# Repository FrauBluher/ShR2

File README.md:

ShR2
====

A redesign of the SHEMP system with a focus on high-bandwidth data acquisition.

Design information and supporting documentation can be found in this repository.

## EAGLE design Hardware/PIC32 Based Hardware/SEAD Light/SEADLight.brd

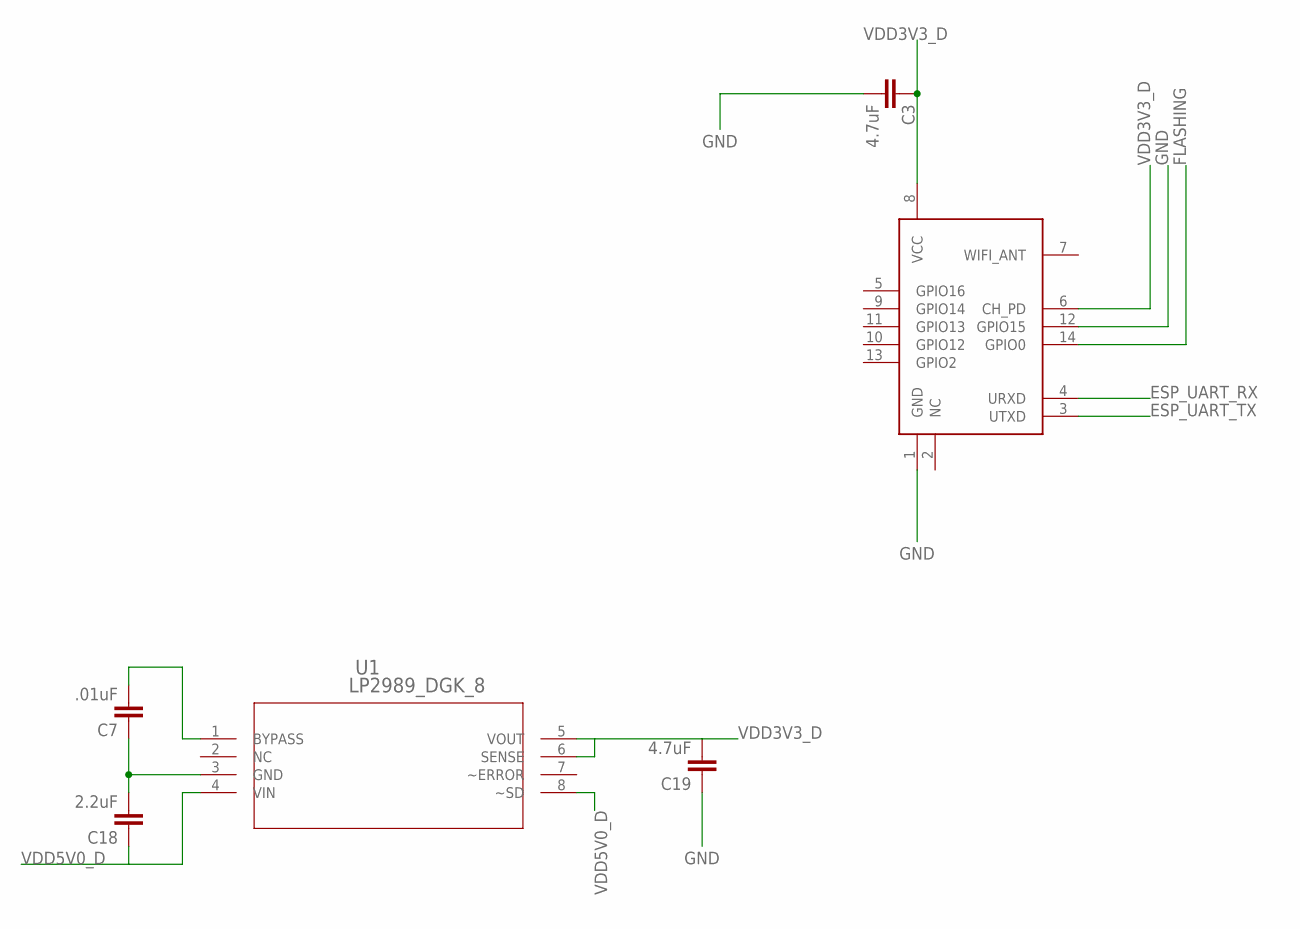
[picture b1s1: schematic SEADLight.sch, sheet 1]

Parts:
C3, C19: 4.7uF; 0805
C7: .01uF; 0805
C18: 2.2uF; 0805
U1: LP2989_DGK_8; MUA08A
U$3: EPS8266; ESP8266-03

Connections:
ESP_UART_RX: U$3.4 (URXD); also elsewhere on the board
ESP_UART_TX: U$3.3 (UTXD); also elsewhere on the board
FLASHING: U$3.14 (GPIO0)
GND: C3.2, C7.1, C18.2, C19.1, U1.3 (GND), U$3.1 (GND), U$3.12 (GPIO15); also elsewhere on the board
unnamed: C7.2, U1.1 (BYPASS)
VDD3V3_D: C3.1, C19.2, U1.5 (VOUT), U1.6 (SENSE), U$3.6 (CH_PD), U$3.8 (VCC); also elsewhere on the board
VDD5V0_D: C18.1, U1.4 (VIN), U1.8 (~SD); also elsewhere on the board

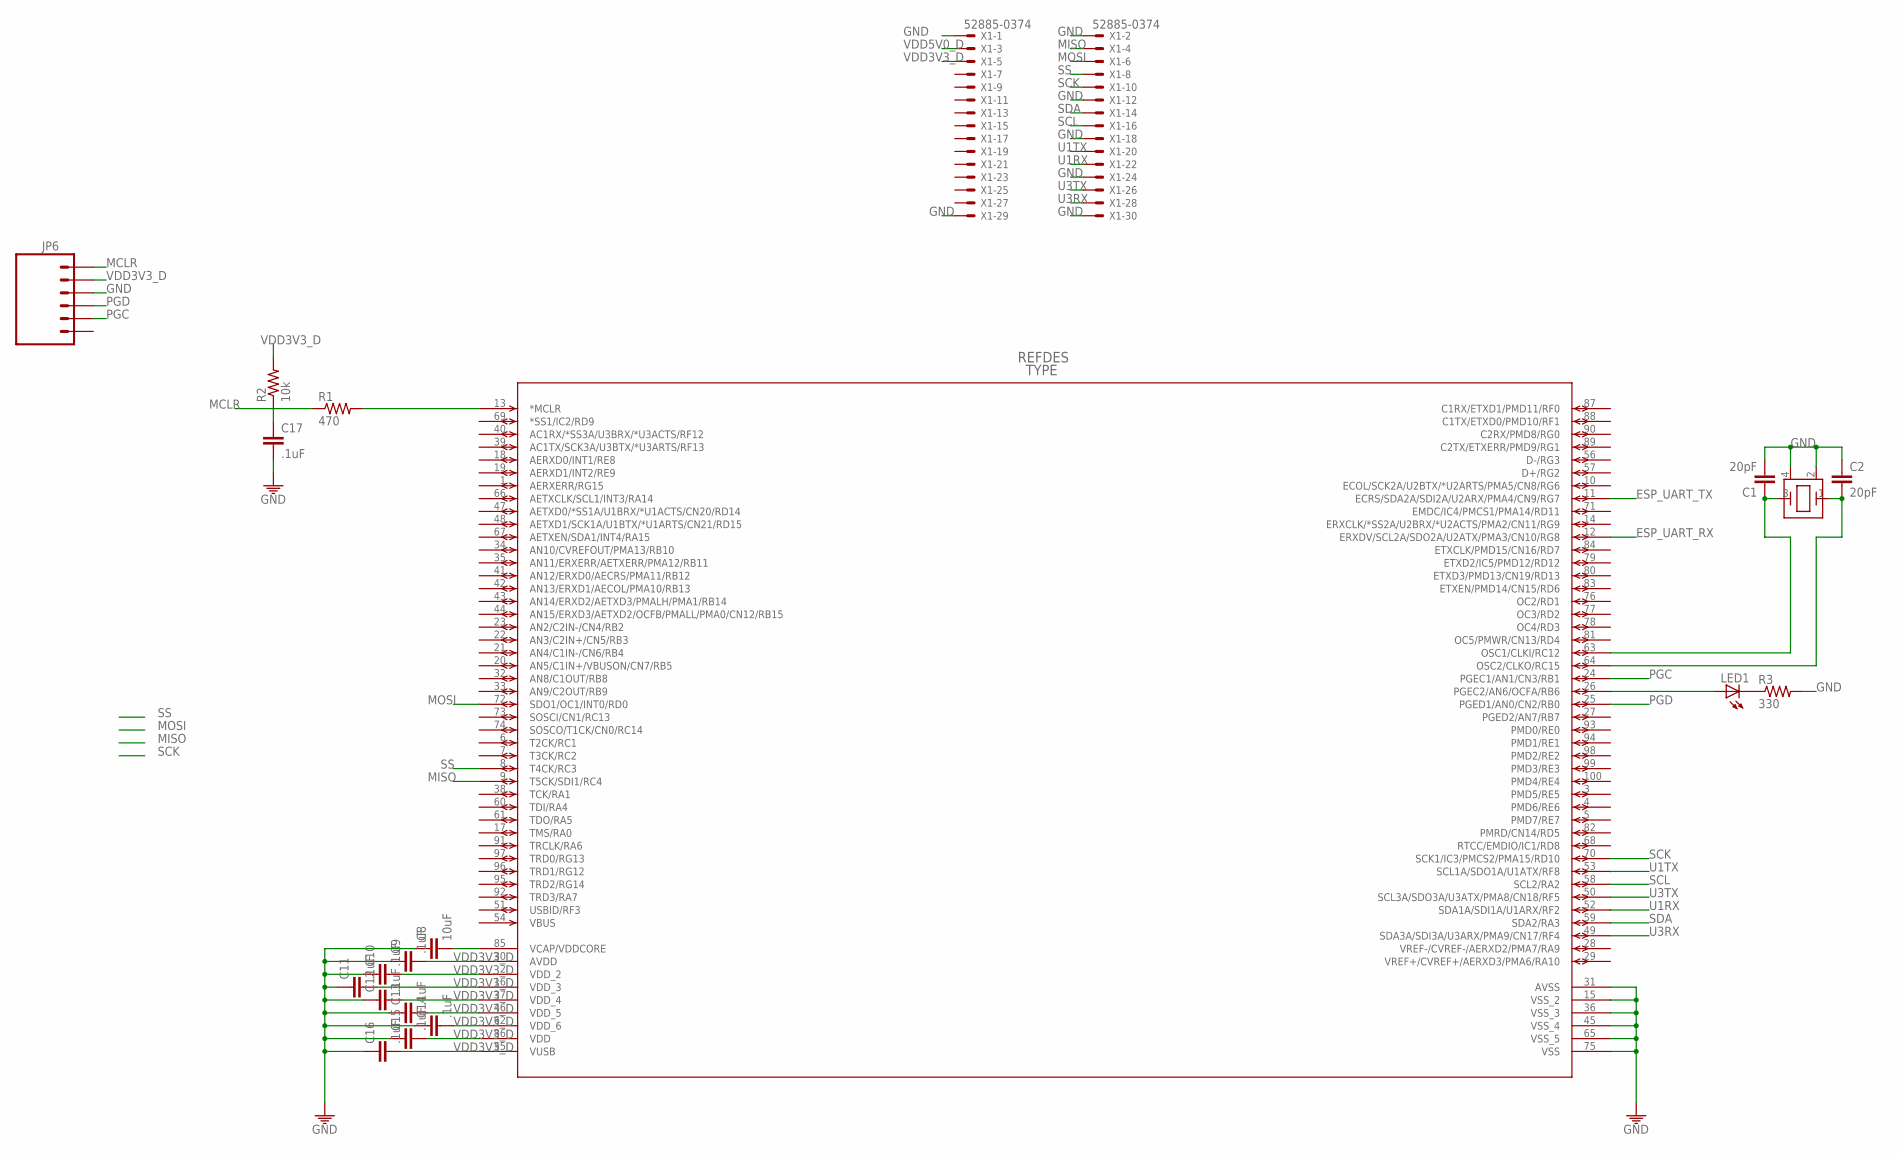
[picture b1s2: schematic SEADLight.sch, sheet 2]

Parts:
C1, C2: 20pF; 0805
C8: 10uF; 0805
C9, C10, C11, C12, C13, C14, C15, C16, C17: .1uF; 0805
JP6: M06SIP_LOCK; 1X06-SIP_LOCK
LED1: LED0805; LED-0805
R1: 470; 0805
R2: 10k; 0805
R3: 330; 0805
U$1: PIC32MX795F512L-; TQFP100_12X12MC
U$2: ABM3B-8.000MHZ-10-1-U-T; ABM3B
X1: 52885-0374

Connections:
ESP_UART_RX: U$1.12 (ERXDV/SCL2A/SDO2A/U2ATX/PMA3/CN10/RG8); also elsewhere on the board
ESP_UART_TX: U$1.11 (ECRS/SDA2A/SDI2A/U2ARX/PMA4/CN9/RG7); also elsewhere on the board
GND: C1.2, C2.1, C8.1, C9.1, C10.1, C11.1, C12.1, C13.1, C14.1, C15.1, C16.1, C17.2, JP6.3, R3.2, U$1.15 (VSS_2), U$1.31 (AVSS), U$1.36 (VSS_3), U$1.45 (VSS_4), U$1.65 (VSS_5), U$1.75 (VSS), U$2.2 (GND1), U$2.4 (GND2), X1.1, X1.2, X1.12, X1.18, X1.24, X1.29, X1.30; also elsewhere on the board
MCLR: C17.1, JP6.1, R1.1, R2.1
MISO: U$1.9 (T5CK/SDI1/RC4), X1.4
MOSI: U$1.72 (SDO1/OC1/INT0/RD0), X1.6
unnamed: C1.1, U$1.63 (OSC1/CLKI/RC12), U$2.3 (OSC2)
unnamed: C2.2, U$1.64 (OSC2/CLKO/RC15), U$2.1 (OSC1)
unnamed: C8.2, U$1.85 (VCAP/VDDCORE)
unnamed: R1.2, U$1.13 (*MCLR)
unnamed: LED1.1 (A), U$1.26 (PGEC2/AN6/OCFA/RB6)
unnamed: LED1.2 (C), R3.1
PGC: JP6.5, U$1.24 (PGEC1/AN1/CN3/RB1)
PGD: JP6.4, U$1.25 (PGED1/AN0/CN2/RB0)
SCK: U$1.70 (SCK1/IC3/PMCS2/PMA15/RD10), X1.10
SCL: U$1.58 (SCL2/RA2), X1.16
SDA: U$1.59 (SDA2/RA3), X1.14
SS: U$1.8 (T4CK/RC3), X1.8
U1RX: U$1.52 (SDA1A/SDI1A/U1ARX/RF2), X1.22
U1TX: U$1.53 (SCL1A/SDO1A/U1ATX/RF8), X1.20
U3RX: U$1.49 (SDA3A/SDI3A/U3ARX/PMA9/CN17/RF4), X1.28
U3TX: U$1.50 (SCL3A/SDO3A/U3ATX/PMA8/CN18/RF5), X1.26
VDD3V3_D: C9.2, C10.2, C11.2, C12.2, C13.2, C14.2, C15.2, C16.2, JP6.2, R2.2, U$1.2 (VDD_2), U$1.16 (VDD_3), U$1.30 (AVDD), U$1.37 (VDD_4), U$1.46 (VDD_5), U$1.55 (VUSB), U$1.62 (VDD_6), U$1.86 (VDD), X1.5; also elsewhere on the board
VDD5V0_D: X1.3; also elsewhere on the board

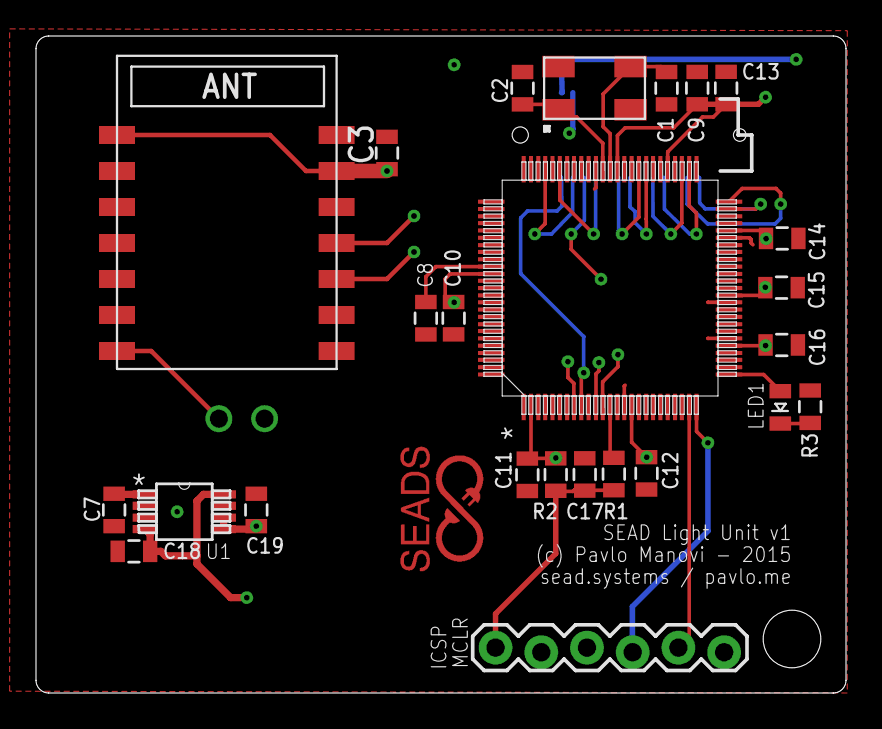
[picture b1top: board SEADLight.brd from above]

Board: 4 copper layers, 45.0 x 36.5 mm, 26 parts (1 on the bottom side), 25 nets.

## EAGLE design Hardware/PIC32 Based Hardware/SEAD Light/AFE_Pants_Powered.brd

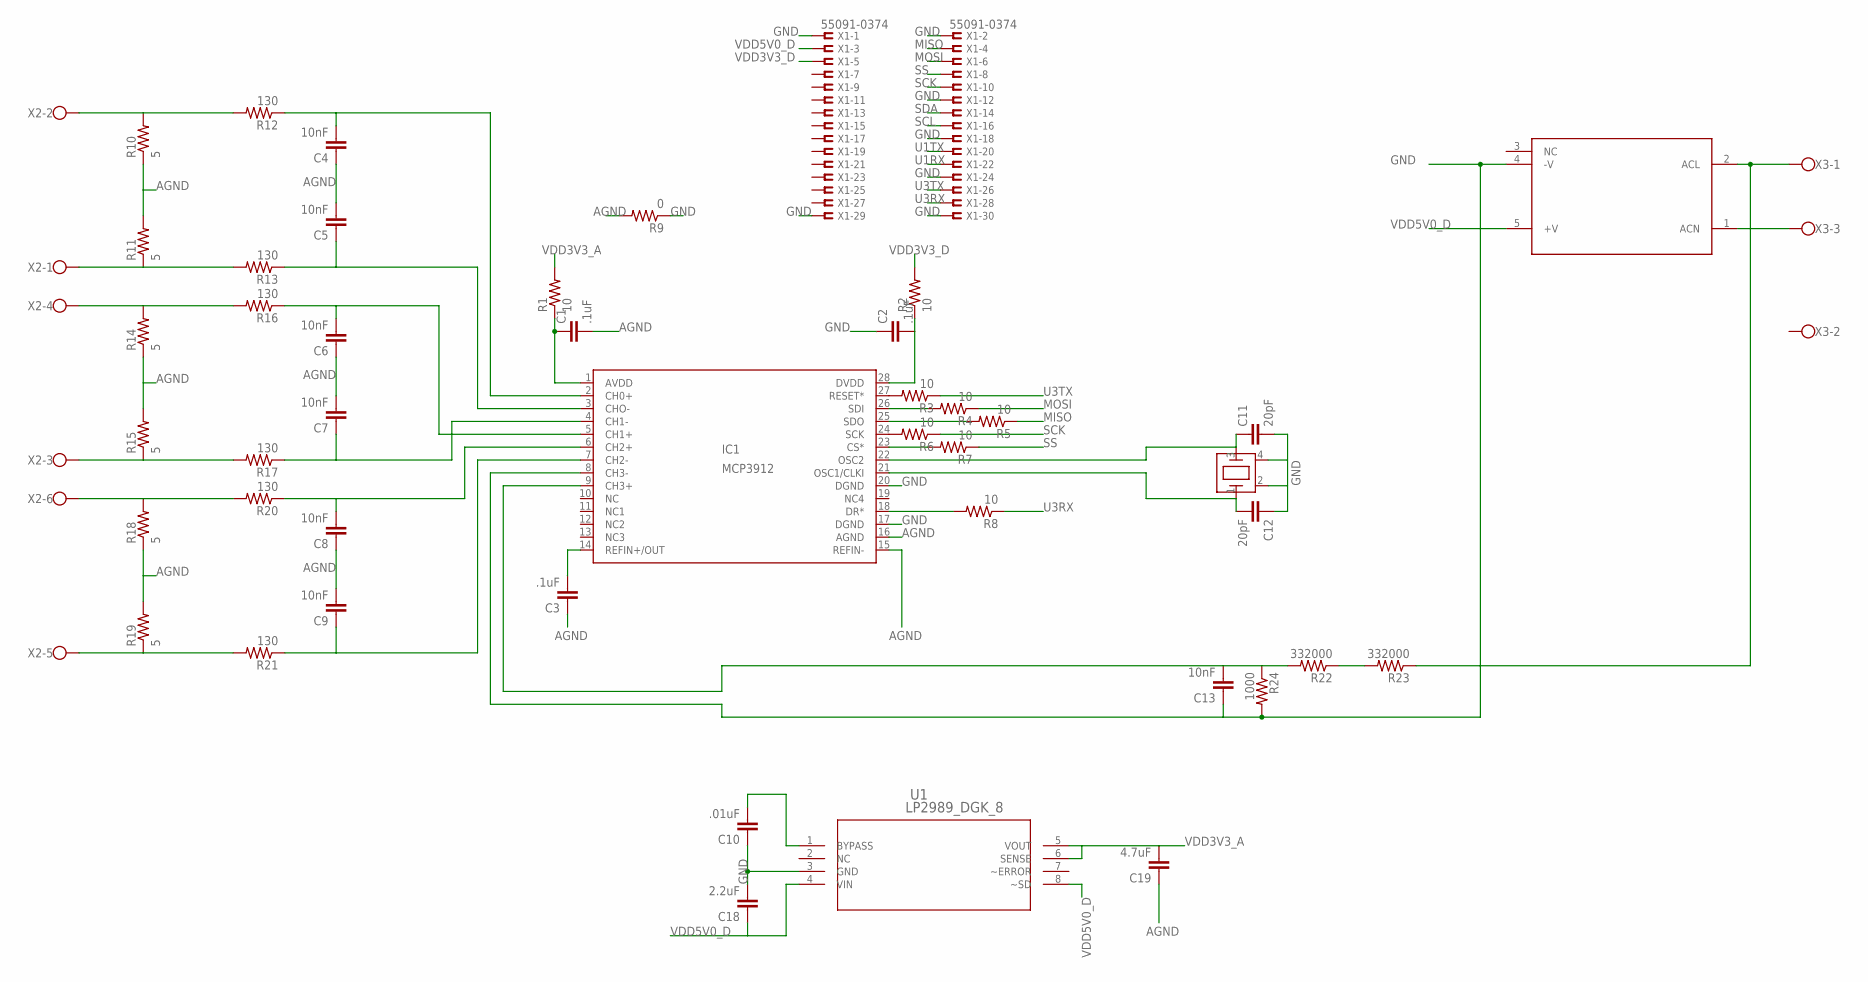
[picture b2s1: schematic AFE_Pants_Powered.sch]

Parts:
C1, C2, C3: .1uF; 0805
C4, C5, C6, C7, C8, C9, C13: 10nF; 0805
C10: .01uF; 0805
C11, C12: 20pF; 0805
C18: 2.2uF; 0805
C19: 4.7uF; 0805
IC1: MCP3912; SSOP28
R1, R2, R3, R4, R5, R6, R7, R8: 10; 0805
R9: 0; 0805
R10, R11, R14, R15, R18, R19: 5; 0805
R12, R13, R16, R17, R20, R21: 130; 0805
R22, R23: 332000; 0805
R24: 1000; 0805
U1: LP2989_DGK_8; MUA08A
U$1: 7M-12.000MEEQ-T; 7M-CRYSTAL
U$2: ECE05US05
X1: 55091-0374
X2: W237-6
X3: W237-103

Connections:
AGND: C1.2, C3.1, C4.1, C5.2, C6.1, C7.2, C8.1, C9.2, C19.1, IC1.15 (REFIN-), IC1.16 (AGND), R9.2, R10.1, R11.2, R14.1, R15.2, R18.1, R19.2
GND: C2.1, C10.1, C11.2, C12.1, C13.1, C18.2, IC1.8 (CH3-), IC1.17 (DGND), IC1.20 (DGND), R9.1, R24.2, U1.3 (GND), U$1.2 (GND1), U$1.4 (GND2), U$2.4 (-V), X1.1, X1.2, X1.12, X1.18, X1.24, X1.29, X1.30
MISO: R5.1, X1.4
MOSI: R4.1, X1.6
unnamed: C1.1, IC1.1 (AVDD), R1.1
unnamed: IC1.27 (RESET*), R3.2
unnamed: IC1.26 (SDI), R4.2
unnamed: IC1.25 (SDO), R5.2
unnamed: IC1.24 (SCK), R6.2
unnamed: IC1.23 (CS*), R7.2
unnamed: IC1.18 (DR*), R8.2
unnamed: C2.2, IC1.28 (DVDD), R2.1
unnamed: C3.2, IC1.14 (REFIN+/OUT)
unnamed: R10.2, R12.2, X2.2
unnamed: R11.1, R13.2, X2.1
unnamed: R14.2, R16.2, X2.4
unnamed: C4.2, IC1.2 (CH0+), R12.1
unnamed: C5.1, IC1.3 (CHO-), R13.1
unnamed: R15.1, R17.2, X2.3
unnamed: C6.2, IC1.5 (CH1+), R16.1
unnamed: C7.1, IC1.4 (CH1-), R17.1
unnamed: R18.2, R20.2, X2.6
unnamed: R19.1, R21.2, X2.5
unnamed: C8.2, IC1.6 (CH2+), R20.1
unnamed: C9.1, IC1.7 (CH2-), R21.1
unnamed: C13.2, IC1.9 (CH3+), R22.2, R24.1
unnamed: C10.2, U1.1 (BYPASS)
unnamed: C11.1, IC1.22 (OSC2), U$1.3 (OSC2)
unnamed: C12.2, IC1.21 (OSC1/CLKI), U$1.1 (OSC1)
unnamed: R23.1, U$2.2 (ACL), X3.1
unnamed: U$2.1 (ACN), X3.3
unnamed: R22.1, R23.2
SCK: R6.1, X1.10
SCL: X1.16
SDA: X1.14
SS: R7.1, X1.8
U1RX: X1.22
U1TX: X1.20
U3RX: R8.1, X1.28
U3TX: R3.1, X1.26
VDD3V3_A: C19.2, R1.2, U1.5 (VOUT), U1.6 (SENSE)
VDD3V3_D: R2.2, X1.5
VDD5V0_D: C18.1, U1.4 (VIN), U1.8 (~SD), U$2.5 (+V), X1.3

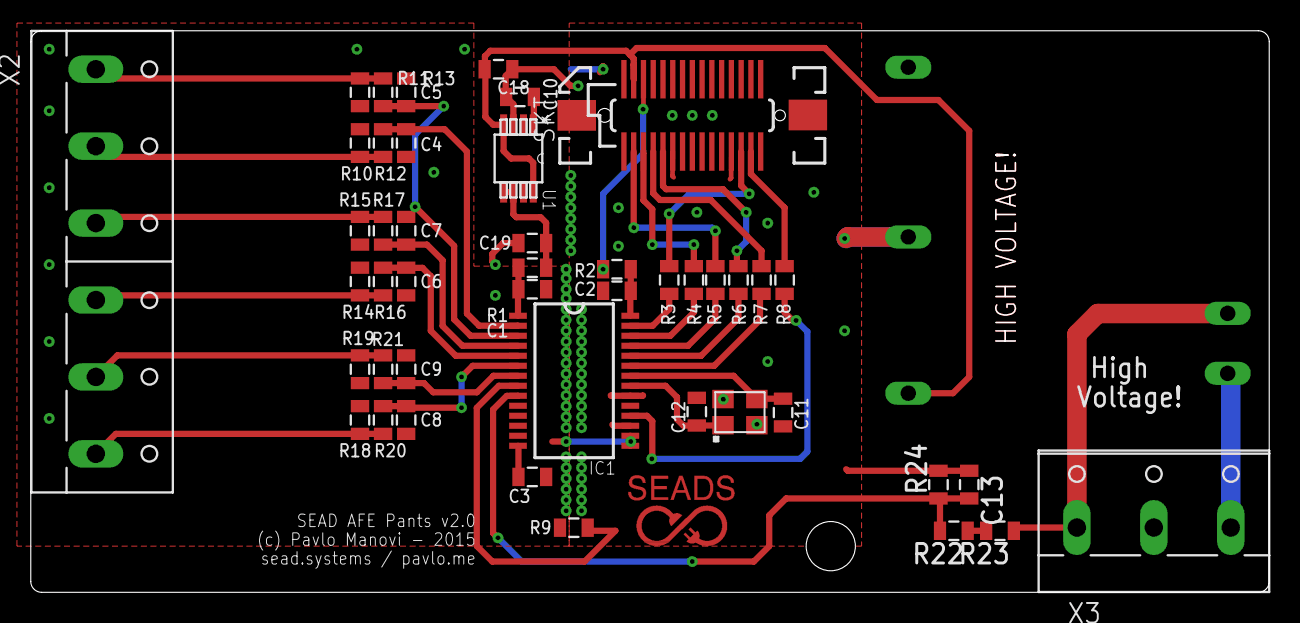
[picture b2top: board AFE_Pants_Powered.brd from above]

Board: 2 copper layers, 80.5 x 36.5 mm, 46 parts (0 on the bottom side), 39 nets.

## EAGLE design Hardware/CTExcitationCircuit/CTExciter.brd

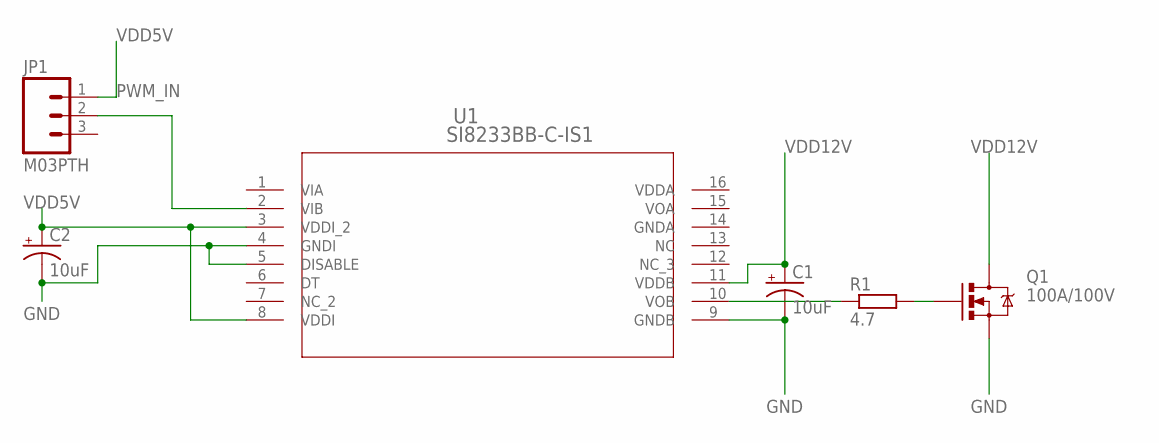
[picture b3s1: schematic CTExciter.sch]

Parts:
C1, C2: 10uF; CPOL-RADIAL-10UF-25V
JP1: M03PTH; 1X03
Q1: 100A/100V; TO-263/D2PAK
R1: 4.7; R0805
U1: SI8233BB-C-IS1; SOIC-16

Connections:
GND: C1.2 (-), C2.2 (-), Q1.3 (S), U1.4 (GNDI), U1.5 (DISABLE), U1.9 (GNDB)
unnamed: R1.1, U1.10 (VOB)
unnamed: Q1.1 (G), R1.2
PWM_IN: JP1.2, U1.2 (VIB)
VDD5V: C2.1 (+), JP1.1, U1.3 (VDDI_2), U1.8 (VDDI)
VDD12V: C1.1 (+), Q1.2 (D), U1.11 (VDDB)

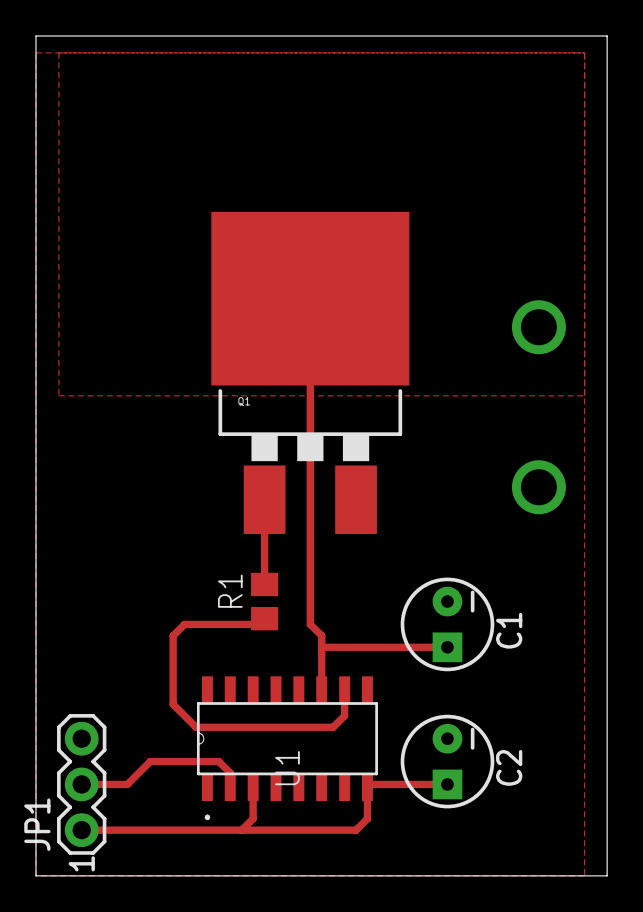
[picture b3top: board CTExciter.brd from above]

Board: 2 copper layers, 31.7 x 46.7 mm, 6 parts (0 on the bottom side), 6 nets.

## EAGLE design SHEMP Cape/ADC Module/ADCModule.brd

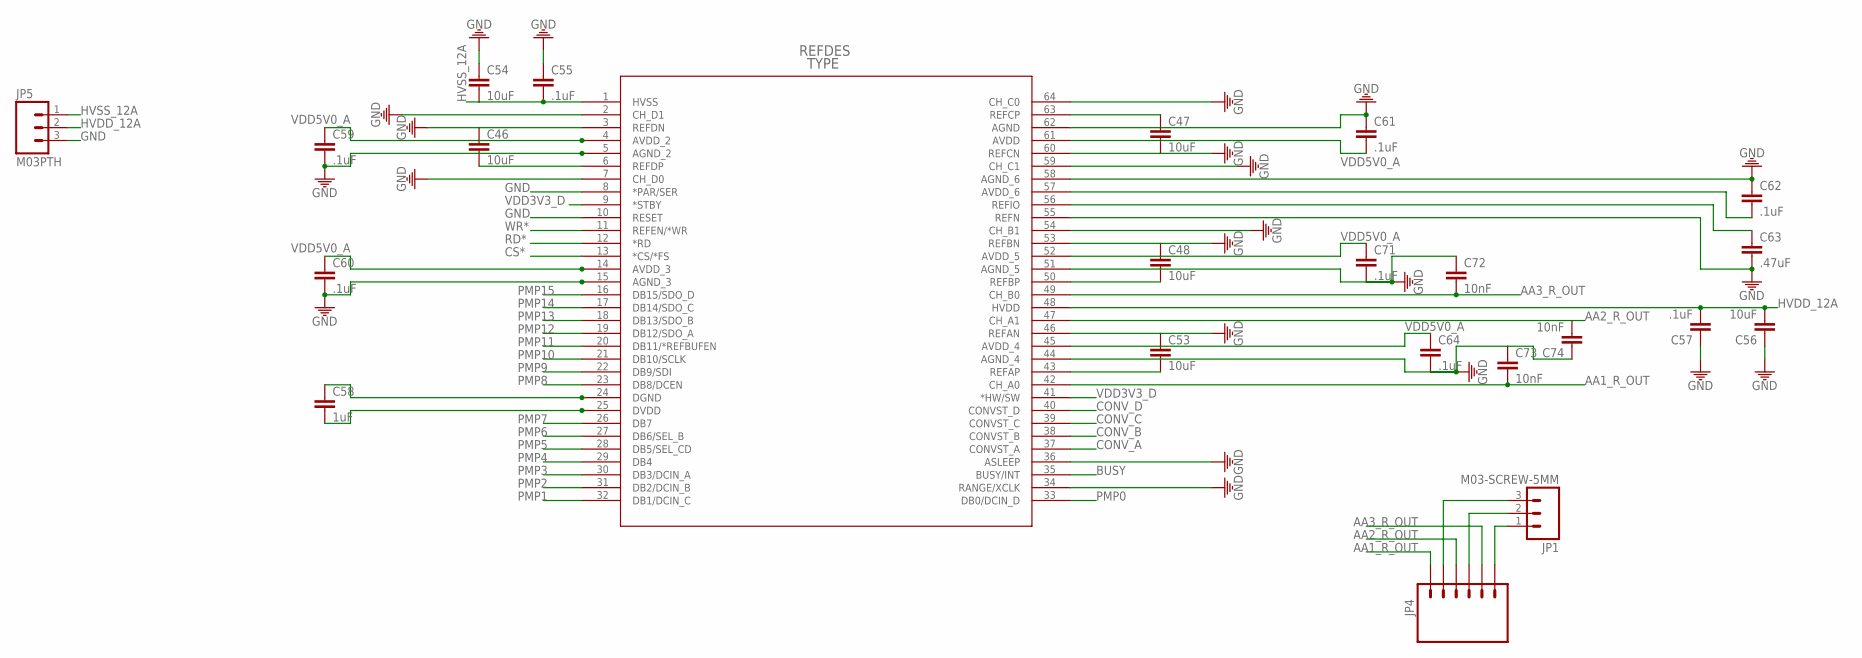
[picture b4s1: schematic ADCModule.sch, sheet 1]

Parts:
C46, C47, C48, C53, C54, C56: 10uF; 0805
C55, C57, C59, C60, C61, C62, C64, C71: .1uF; 0805
C58: 1uF; 0805
C63: .47uF; 0805
C72, C73, C74: 10nF; 0805
JP1: M03-SCREW-5MM; SCREWTERMINAL-5MM-3
JP4: M06SIP; 1X06
JP5: M03PTH; 1X03
U1: ADS8568_PM_64; PM64

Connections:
AA1_R_OUT: C73.2, JP4.1, U1.42 (CH_A0)
AA2_R_OUT: C74.2, JP4.3, U1.47 (CH_A1)
AA3_R_OUT: C72.2, JP4.5, U1.49 (CH_B0)
BUSY: U1.35 (BUSY/INT); also elsewhere on the board
CONV_A: U1.37 (CONVST_A); also elsewhere on the board
CONV_B: U1.38 (CONVST_B); also elsewhere on the board
CONV_C: U1.39 (CONVST_C)
CONV_D: U1.40 (CONVST_D)
CS*: U1.13 (*CS/*FS); also elsewhere on the board
GND: C46.1, C47.2, C48.1, C53.1, C54.1, C55.1, C56.1, C57.1, C58.1, C59.2, C60.2, C61.1, C62.1, C63.2, C64.2, C71.2, C72.1, C73.1, C74.1, JP5.3, U1.2 (CH_D1), U1.3 (REFDN), U1.5 (AGND_2), U1.7 (CH_D0), U1.8 (*PAR/SER), U1.10 (RESET), U1.15 (AGND_3), U1.24 (DGND), U1.34 (RANGE/XCLK), U1.36 (ASLEEP), U1.44 (AGND_4), U1.46 (REFAN), U1.51 (AGND_5), U1.53 (REFBN), U1.54 (CH_B1), U1.55 (REFN), U1.58 (AGND_6), U1.59 (CH_C1), U1.60 (REFCN), U1.62 (AGND), U1.64 (CH_C0); also elsewhere on the board
HVSS_12A: C54.2, C55.2, JP5.1, U1.1 (HVSS)
unnamed 14: JP1.3, JP4.2; also elsewhere on the board
unnamed 15: JP1.2, JP4.4; also elsewhere on the board
unnamed 16: JP1.1, JP4.6; also elsewhere on the board
unnamed: C63.1, U1.56 (REFIO)
unnamed: C46.2, U1.6 (REFDP)
unnamed: C53.2, U1.43 (REFAP)
unnamed: C48.2, U1.50 (REFBP)
unnamed: C47.1, U1.63 (REFCP)
PMP0: U1.33 (DB0/DCIN_D); also elsewhere on the board
PMP1: U1.32 (DB1/DCIN_C); also elsewhere on the board
PMP2: U1.31 (DB2/DCIN_B); also elsewhere on the board
PMP3: U1.30 (DB3/DCIN_A); also elsewhere on the board
PMP4: U1.29 (DB4); also elsewhere on the board
PMP5: U1.28 (DB5/SEL_CD); also elsewhere on the board
PMP6: U1.27 (DB6/SEL_B); also elsewhere on the board
PMP7: U1.26 (DB7); also elsewhere on the board
PMP8: U1.23 (DB8/DCEN); also elsewhere on the board
PMP9: U1.22 (DB9/SDI); also elsewhere on the board
PMP10: U1.21 (DB10/SCLK); also elsewhere on the board
PMP11: U1.20 (DB11/*REFBUFEN); also elsewhere on the board
PMP12: U1.19 (DB12/SDO_A); also elsewhere on the board
PMP13: U1.18 (DB13/SDO_B); also elsewhere on the board
PMP14: U1.17 (DB14/SDO_C); also elsewhere on the board
PMP15: U1.16 (DB15/SDO_D); also elsewhere on the board
RD*: U1.12 (*RD); also elsewhere on the board
VDD3V3_D: C58.2, U1.9 (*STBY), U1.25 (DVDD), U1.41 (*HW/SW); also elsewhere on the board
WR*: U1.11 (REFEN/*WR); also elsewhere on the board

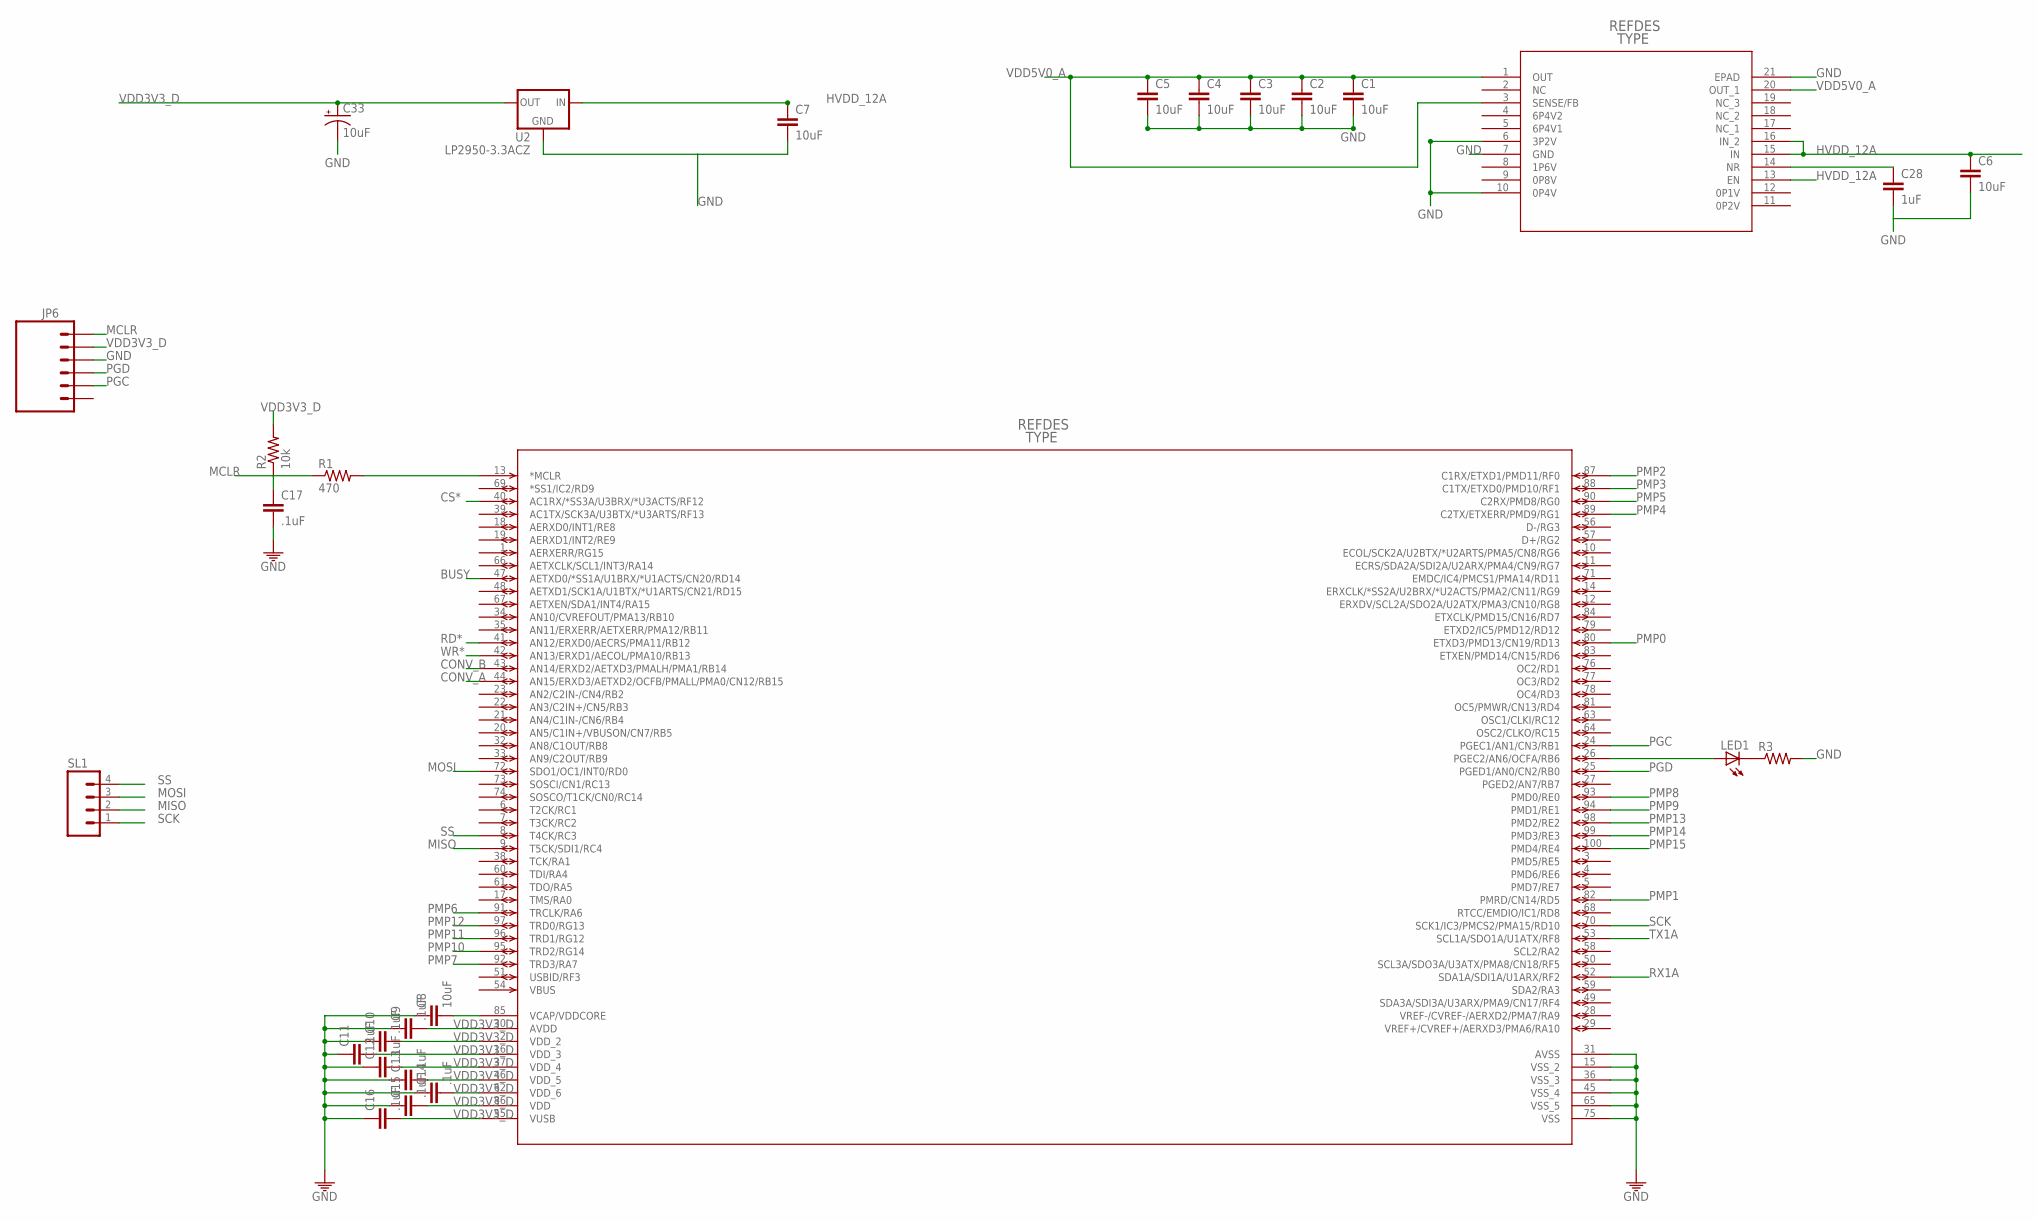
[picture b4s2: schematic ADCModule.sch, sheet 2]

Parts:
C1, C2, C3, C4, C5, C6, C7: 10uF; 0805
C8: 10uF; 1206
C9, C10, C11, C12, C13, C14, C15, C16, C17: .1uF; 0805
C28: 1uF; 0805
C33: 10uF; CPOL-RADIAL-10UF-25V
JP6: M06SIP_LOCK; 1X06-SIP_LOCK
LED1: LED0805; LED-0805
R1: 470; 0805
R2: 10k; 0805
R3: RESISTOR0805-RES; 0805
SL1: M04LOCK; 1X04_LOCK
U2: LP2950-3.3ACZ; TO92
U$1: PIC32MX795F512L-; TQFP100_12X12MC
U$3: TPS7A4700_RGW_20; RGW20_3P15X3P15

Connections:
BUSY: U$1.47 (AETXD0/*SS1A/U1BRX/*U1ACTS/CN20/RD14); also elsewhere on the board
CONV_A: U$1.44 (AN15/ERXD3/AETXD2/OCFB/PMALL/PMA0/CN12/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); also elsewhere on the board
CONV_B: U$1.43 (AN14/ERXD2/AETXD3/PMALH/PMA1/RB14); also elsewhere on the board
CS*: U$1.40 (AC1RX/*SS3A/U3BRX/*U3ACTS/RF12); also elsewhere on the board
GND: C1.2, C2.2, C3.2, C4.2, C5.2, C6.2, C7.2, C8.1, C9.1, C10.1, C11.1, C12.1, C13.1, C14.1, C15.1, C16.1, C17.2, C28.2, C33.2 (-), JP6.3, R3.2, U2.2 (GND), U$1.15 (VSS_2), U$1.31 (AVSS), U$1.36 (VSS_3), U$1.45 (VSS_4), U$1.65 (VSS_5), U$1.75 (VSS), U$3.6 (3P2V), U$3.7 (GND), U$3.10 (0P4V), U$3.21 (EPAD); also elsewhere on the board
MCLR: C17.1, JP6.1, R1.1, R2.1
MISO: SL1.2, U$1.9 (T5CK/SDI1/RC4)
MOSI: SL1.3, U$1.72 (SDO1/OC1/INT0/RD0)
unnamed: C8.2, U$1.85 (VCAP/VDDCORE)
unnamed: R1.2, U$1.13 (*MCLR)
unnamed: LED1.1 (A), U$1.26 (PGEC2/AN6/OCFA/RB6)
unnamed: LED1.2 (C), R3.1
unnamed: C28.1, U$3.14 (NR)
PGC: JP6.5, U$1.24 (PGEC1/AN1/CN3/RB1)
PGD: JP6.4, U$1.25 (PGED1/AN0/CN2/RB0)
PMP0: U$1.80 (ETXD3/PMD13/CN19/RD13); also elsewhere on the board
PMP1: U$1.82 (PMRD/CN14/RD5); also elsewhere on the board
PMP2: U$1.87 (C1RX/ETXD1/PMD11/RF0); also elsewhere on the board
PMP3: U$1.88 (C1TX/ETXD0/PMD10/RF1); also elsewhere on the board
PMP4: U$1.89 (C2TX/ETXERR/PMD9/RG1); also elsewhere on the board
PMP5: U$1.90 (C2RX/PMD8/RG0); also elsewhere on the board
PMP6: U$1.91 (TRCLK/RA6); also elsewhere on the board
PMP7: U$1.92 (TRD3/RA7); also elsewhere on the board
PMP8: U$1.93 (PMD0/RE0); also elsewhere on the board
PMP9: U$1.94 (PMD1/RE1); also elsewhere on the board
PMP10: U$1.95 (TRD2/RG14); also elsewhere on the board
PMP11: U$1.96 (TRD1/RG12); also elsewhere on the board
PMP12: U$1.97 (TRD0/RG13); also elsewhere on the board
PMP13: U$1.98 (PMD2/RE2); also elsewhere on the board
PMP14: U$1.99 (PMD3/RE3); also elsewhere on the board
PMP15: U$1.100 (PMD4/RE4); also elsewhere on the board
RD*: U$1.41 (AN12/ERXD0/AECRS/PMA11/RB12); also elsewhere on the board
SCK: SL1.1, U$1.70 (SCK1/IC3/PMCS2/PMA15/RD10)
SS: SL1.4, U$1.8 (T4CK/RC3)
VDD3V3_D: C9.2, C10.2, C11.2, C12.2, C13.2, C14.2, C15.2, C16.2, C33.1 (+), JP6.2, R2.2, U2.1 (OUT), U$1.2 (VDD_2), U$1.16 (VDD_3), U$1.30 (AVDD), U$1.37 (VDD_4), U$1.46 (VDD_5), U$1.55 (VUSB), U$1.62 (VDD_6), U$1.86 (VDD); also elsewhere on the board
WR*: U$1.42 (AN13/ERXD1/AECOL/PMA10/RB13); also elsewhere on the board

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
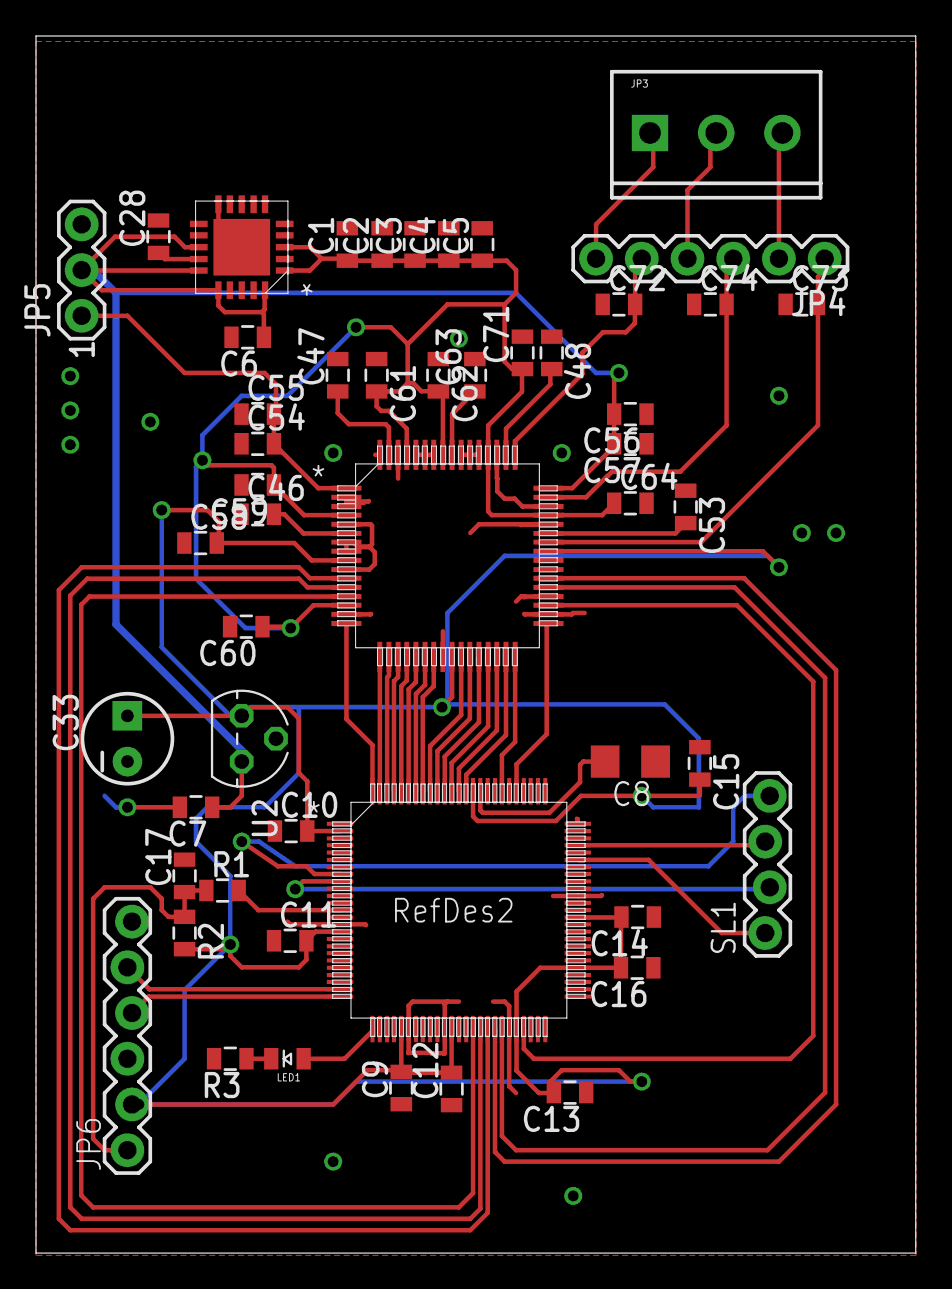
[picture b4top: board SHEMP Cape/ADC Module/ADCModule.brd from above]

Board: 2 copper layers, 48.9 x 67.6 mm, 51 parts (0 on the bottom side), 50 nets.

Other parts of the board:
JP3: M03SCREW_LOCK; SCREWTERMINAL-3.5MM-3_LOCK.007S

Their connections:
unnamed 14: JP3.3; also elsewhere on the board
unnamed 15: JP3.2; also elsewhere on the board
unnamed 16: JP3.1; also elsewhere on the board

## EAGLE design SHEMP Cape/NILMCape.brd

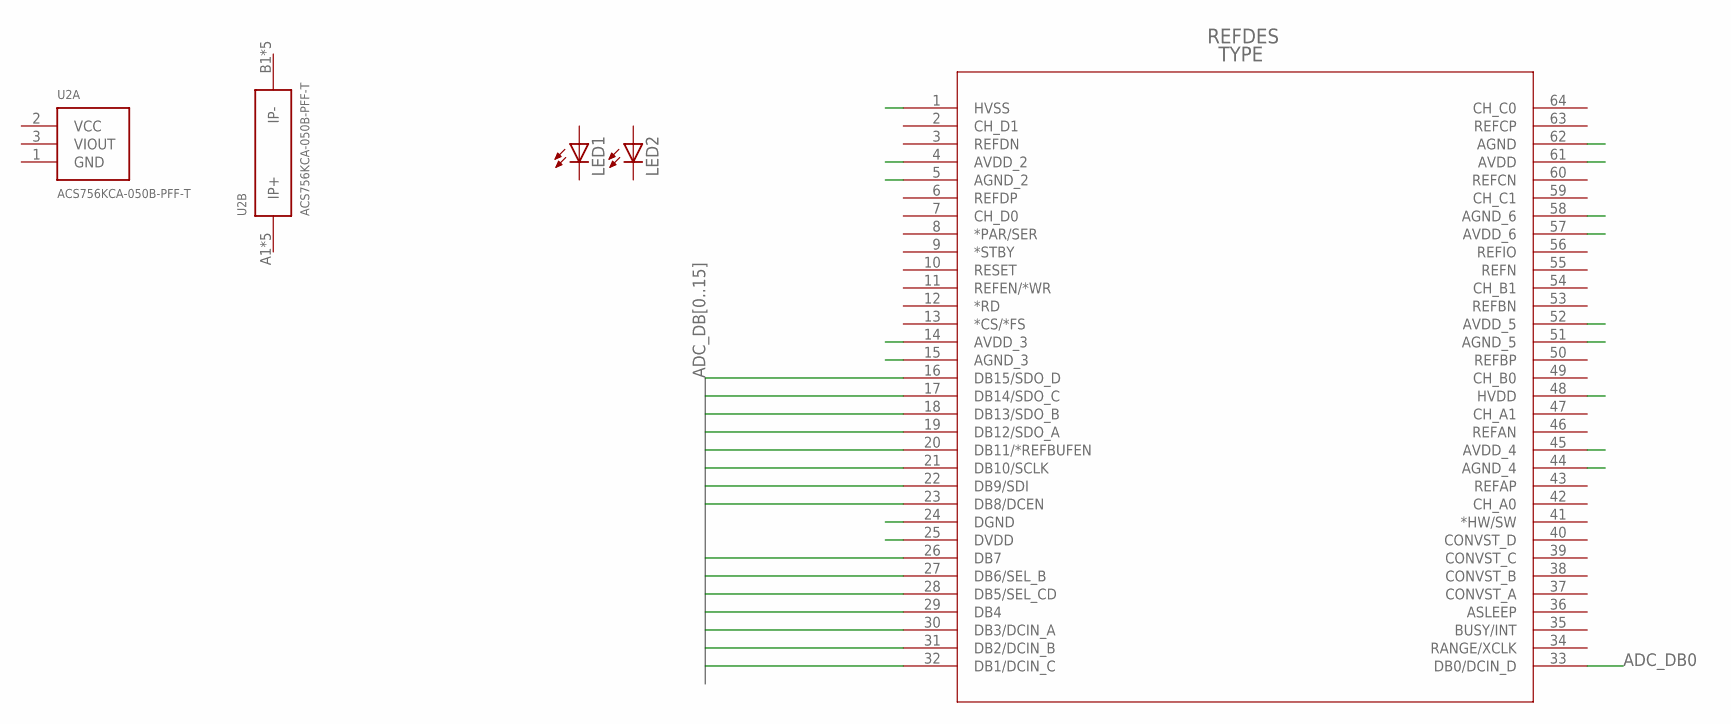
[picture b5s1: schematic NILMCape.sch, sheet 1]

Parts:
LED1, LED2: LED0805; LED-0805
U1: ADS8568_PM_64; PM64
U2: ACS756KCA-050B-PFF-T; 5PFF

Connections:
ADC_DB0: U1.33 (DB0/DCIN_D); also elsewhere on the board
ADC_DB1: U1.32 (DB1/DCIN_C); also elsewhere on the board
ADC_DB2: U1.31 (DB2/DCIN_B); also elsewhere on the board
ADC_DB3: U1.30 (DB3/DCIN_A); also elsewhere on the board
ADC_DB4: U1.29 (DB4); also elsewhere on the board
ADC_DB5: U1.28 (DB5/SEL_CD); also elsewhere on the board
ADC_DB6: U1.27 (DB6/SEL_B); also elsewhere on the board
ADC_DB7: U1.26 (DB7); also elsewhere on the board
ADC_DB8: U1.23 (DB8/DCEN); also elsewhere on the board
ADC_DB9: U1.22 (DB9/SDI); also elsewhere on the board
ADC_DB10: U1.21 (DB10/SCLK); also elsewhere on the board
ADC_DB11: U1.20 (DB11/*REFBUFEN); also elsewhere on the board
ADC_DB12: U1.19 (DB12/SDO_A); also elsewhere on the board
ADC_DB13: U1.18 (DB13/SDO_B); also elsewhere on the board
ADC_DB14: U1.17 (DB14/SDO_C); also elsewhere on the board
ADC_DB15: U1.16 (DB15/SDO_D); also elsewhere on the board
HVSS: U1.1 (HVSS); also elsewhere on the board

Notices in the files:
SEAD Hardware/Filtering/FilterBoard_+-8V_MAX.brd:
(c) 2014 Pavlo Manovi
